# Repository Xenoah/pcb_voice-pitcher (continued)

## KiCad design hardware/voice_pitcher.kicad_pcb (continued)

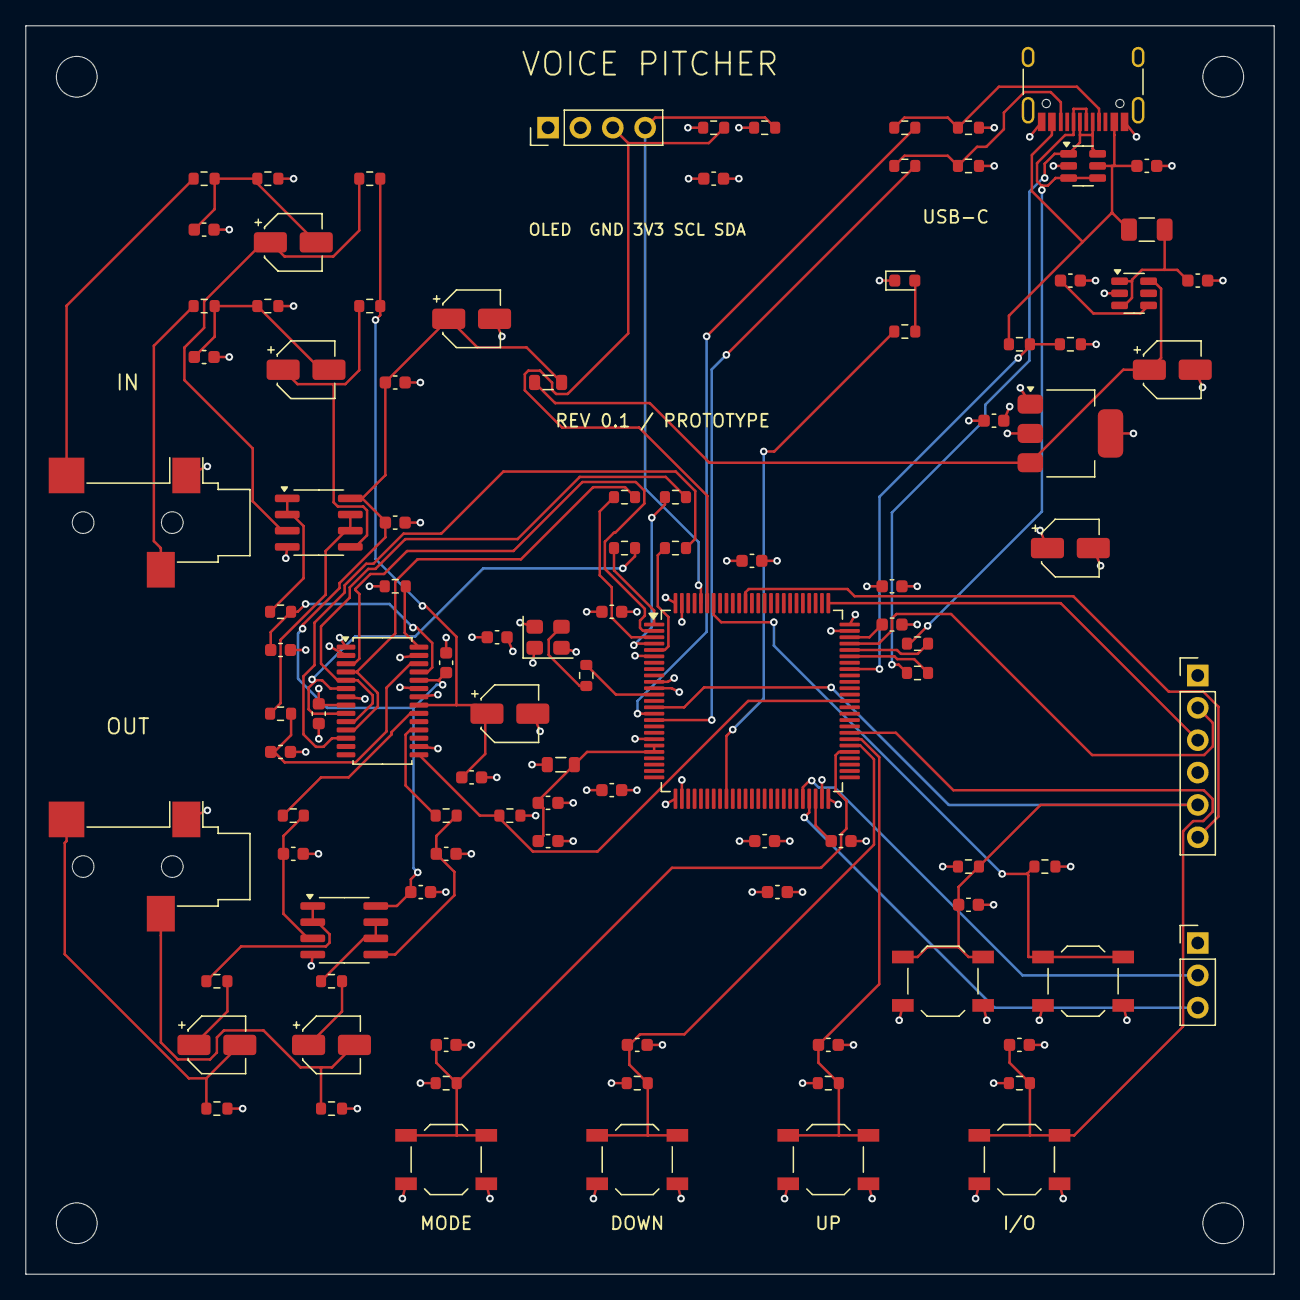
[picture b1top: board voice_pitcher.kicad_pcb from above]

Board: 4 copper layers, 98.0 x 98.0 mm, 107 parts (0 on the bottom side), 68 nets.

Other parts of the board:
H1, H2, H3, H4: M3 NPTH; MountingHole__MountingHole_3.2mm_M3

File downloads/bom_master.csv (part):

ref,value,mpn,lcsc,footprint,assembly,sourcing_status,source_url
C1,100n,CC0603KRX7R9BB104,C14663,Capacitor_SMD:C_0603_1608Metric,SMT,BASIC,https://jlcpcb.com/partdetail/C14663
C2,10u,UWT1C100MCL1GB,,Capacitor_SMD:CP_Elec_4x5.8,SMT,UNVERIFIED,
C3,10u,UWT1C100MCL1GB,,Capacitor_SMD:CP_Elec_4x5.8,SMT,UNVERIFIED,
C4,100n,CC0603KRX7R9BB104,C14663,Capacitor_SMD:C_0603_1608Metric,SMT,BASIC,https://jlcpcb.com/partdetail/C14663
C5,10u,UWT1C100MCL1GB,,Capacitor_SMD:CP_Elec_4x5.8,SMT,UNVERIFIED,
C6,100n,CC0603KRX7R9BB104,C14663,Capacitor_SMD:C_0603_1608Metric,SMT,BASIC,https://jlcpcb.com/partdetail/C14663
C7,100n,CC0603KRX7R9BB104,C14663,Capacitor_SMD:C_0603_1608Metric,SMT,BASIC,https://jlcpcb.com/partdetail/C14663
C8,100n,CC0603KRX7R9BB104,C14663,Capacitor_SMD:C_0603_1608Metric,SMT,BASIC,https://jlcpcb.com/partdetail/C14663
C9,100n,CC0603KRX7R9BB104,C14663,Capacitor_SMD:C_0603_1608Metric,SMT,BASIC,https://jlcpcb.com/partdetail/C14663
C10,100n,CC0603KRX7R9BB104,C14663,Capacitor_SMD:C_0603_1608Metric,SMT,BASIC,https://jlcpcb.com/partdetail/C14663
C11,100n,CC0603KRX7R9BB104,C14663,Capacitor_SMD:C_0603_1608Metric,SMT,BASIC,https://jlcpcb.com/partdetail/C14663
C12,100n,CC0603KRX7R9BB104,C14663,Capacitor_SMD:C_0603_1608Metric,SMT,BASIC,https://jlcpcb.com/partdetail/C14663
C13,1u,GRM188R71C105KA12D,,Capacitor_SMD:C_0603_1608Metric,SMT,UNVERIFIED,
C14,2.2u,GRM188R61C225KE15D,,Capacitor_SMD:C_0603_1608Metric,SMT,UNVERIFIED,
C15,2.2u,GRM188R61C225KE15D,,Capacitor_SMD:C_0603_1608Metric,SMT,UNVERIFIED,
C16,4.7u,GRM188R61C475KE11D,,Capacitor_SMD:C_0603_1608Metric,SMT,UNVERIFIED,
C17,100n,CC0603KRX7R9BB104,C14663,Capacitor_SMD:C_0603_1608Metric,SMT,BASIC,https://jlcpcb.com/partdetail/C14663
C18,100n,CC0603KRX7R9BB104,C14663,Capacitor_SMD:C_0603_1608Metric,SMT,BASIC,https://jlcpcb.com/partdetail/C14663
C19,100n,CC0603KRX7R9BB104,C14663,Capacitor_SMD:C_0603_1608Metric,SMT,BASIC,https://jlcpcb.com/partdetail/C14663
C20,100n,CC0603KRX7R9BB104,C14663,Capacitor_SMD:C_0603_1608Metric,SMT,BASIC,https://jlcpcb.com/partdetail/C14663
C21,10u,UWT1C100MCL1GB,,Capacitor_SMD:CP_Elec_4x5.8,SMT,UNVERIFIED,
C22,100n,CC0603KRX7R9BB104,C14663,Capacitor_SMD:C_0603_1608Metric,SMT,BASIC,https://jlcpcb.com/partdetail/C14663
C23,100n,CC0603KRX7R9BB104,C14663,Capacitor_SMD:C_0603_1608Metric,SMT,BASIC,https://jlcpcb.com/partdetail/C14663
C24,470p,GRM1885C1H471JA01D,,Capacitor_SMD:C_0603_1608Metric,SMT,UNVERIFIED,
C25,4.7u,UWT1C4R7MCL1GB,,Capacitor_SMD:CP_Elec_4x5.8,SMT,UNVERIFIED,
C26,2.2n,GRM1885C1H222JA01D,,Capacitor_SMD:C_0603_1608Metric,SMT,UNVERIFIED,
C29,470p,GRM1885C1H471JA01D,,Capacitor_SMD:C_0603_1608Metric,SMT,UNVERIFIED,
C30,4.7u,UWT1C4R7MCL1GB,,Capacitor_SMD:CP_Elec_4x5.8,SMT,UNVERIFIED,
C31,2.2n,GRM1885C1H222JA01D,,Capacitor_SMD:C_0603_1608Metric,SMT,UNVERIFIED,
C34,100n,CC0603KRX7R9BB104,C14663,Capacitor_SMD:C_0603_1608Metric,SMT,BASIC,https://jlcpcb.com/partdetail/C14663
C35,1n,GRM1885C1H102JA01D,,Capacitor_SMD:C_0603_1608Metric,SMT,UNVERIFIED,
C36,10u,UWT1C100MCL1GB,,Capacitor_SMD:CP_Elec_4x5.8,SMT,UNVERIFIED,
C40,1n,GRM1885C1H102JA01D,,Capacitor_SMD:C_0603_1608Metric,SMT,UNVERIFIED,
C41,10u,UWT1C100MCL1GB,,Capacitor_SMD:CP_Elec_4x5.8,SMT,UNVERIFIED,
C42,100n,CC0603KRX7R9BB104,C14663,Capacitor_SMD:C_0603_1608Metric,SMT,BASIC,https://jlcpcb.com/partdetail/C14663
C43,100n,CC0603KRX7R9BB104,C14663,Capacitor_SMD:C_0603_1608Metric,SMT,BASIC,https://jlcpcb.com/partdetail/C14663
C44,100n,CC0603KRX7R9BB104,C14663,Capacitor_SMD:C_0603_1608Metric,SMT,BASIC,https://jlcpcb.com/partdetail/C14663
C45,100n,CC0603KRX7R9BB104,C14663,Capacitor_SMD:C_0603_1608Metric,SMT,BASIC,https://jlcpcb.com/partdetail/C14663
C46,100n,CC0603KRX7R9BB104,C14663,Capacitor_SMD:C_0603_1608Metric,SMT,BASIC,https://jlcpcb.com/partdetail/C14663
C47,1u,GRM188R71C105KA12D,,Capacitor_SMD:C_0603_1608Metric,SMT,UNVERIFIED,
C48,10n,GRM188R71E103KA01D,,Capacitor_SMD:C_0603_1608Metric,SMT,UNVERIFIED,
D1,GREEN,LTST-C190KGKT,,LED_SMD:LED_0603_1608Metric,SMT,UNVERIFIED,
F1,500mA PTC,1206L050YR,,Fuse:Fuse_1206_3216Metric,SMT,UNVERIFIED,
FB1,120R@100MHz,BLM21PG121SN1D,,Inductor_SMD:L_0805_2012Metric,SMT,UNVERIFIED,
FB2,120R@100MHz,BLM21PG121SN1D,,Inductor_SMD:L_0805_2012Metric,SMT,UNVERIFIED,
H1,M3 NPTH,M3 NPTH,,MountingHole:MountingHole_3.2mm_M3,MECHANICAL,MECHANICAL,
H2,M3 NPTH,M3 NPTH,,MountingHole:MountingHole_3.2mm_M3,MECHANICAL,MECHANICAL,
H3,M3 NPTH,M3 NPTH,,MountingHole:MountingHole_3.2mm_M3,MECHANICAL,MECHANICAL,
H4,M3 NPTH,M3 NPTH,,MountingHole:MountingHole_3.2mm_M3,MECHANICAL,MECHANICAL,
J1,USB-C USB2 DEVICE,TYPE-C-31-M-12,C165948,Connector_USB:USB_C_Receptacle_HRO_TYPE-C-31-M-12,SMT,JLC_LISTED,https://jlcpcb.com/partdetail/C165948
J2,3.5mm STEREO IN,SJ-3523-SMT-TR,,Connector_Audio:Jack_3.5mm_CUI_SJ-3523-SMT_Horizontal,SMT,UNVERIFIED,
J3,3.5mm STEREO OUT,SJ-3523-SMT-TR,,Connector_Audio:Jack_3.5mm_CUI_SJ-3523-SMT_Horizontal,SMT,UNVERIFIED,
J4,OLED GND VCC SCL SDA,1x4 2.54mm OLED socket,,Connector_PinHeader_2.54mm:PinHeader_1x04_P2.54mm_Vertical,HAND,HAND,
J5,SWD,1x6 2.54mm header,,Connector_PinHeader_2.54mm:PinHeader_1x06_P2.54mm_Vertical,HAND,HAND,
J6,UART 3V3,1x3 2.54mm header,,Connector_PinHeader_2.54mm:PinHeader_1x03_P2.54mm_Vertical,HAND,HAND,
R1,5.1k,0603WAF5101T5E,C23186,Resistor_SMD:R_0603_1608Metric,SMT,BASIC,https://jlcpcb.com/partdetail/C23186
R2,5.1k,0603WAF5101T5E,C23186,Resistor_SMD:R_0603_1608Metric,SMT,BASIC,https://jlcpcb.com/partdetail/C23186
R3,1k,0603WAF1001T5E,C21190,Resistor_SMD:R_0603_1608Metric,SMT,BASIC,https://jlcpcb.com/partdetail/C21190
R4,1k,0603WAF1001T5E,C21190,Resistor_SMD:R_0603_1608Metric,SMT,BASIC,https://jlcpcb.com/partdetail/C21190
R5,22,0603WAF220JT5E,C23345,Resistor_SMD:R_0603_1608Metric,SMT,BASIC,https://jlcpcb.com/partdetail/C23345
R6,22,0603WAF220JT5E,C23345,Resistor_SMD:R_0603_1608Metric,SMT,BASIC,https://jlcpcb.com/partdetail/C23345
R7,100k,0603WAF1003T5E,C25803,Resistor_SMD:R_0603_1608Metric,SMT,BASIC,https://jlcpcb.com/partdetail/C25803
R8,100k,0603WAF1003T5E,C25803,Resistor_SMD:R_0603_1608Metric,SMT,BASIC,https://jlcpcb.com/partdetail/C25803
R9,33,0603WAF330JT5E,C23140,Resistor_SMD:R_0603_1608Metric,SMT,JLC_LISTED,https://jlcpcb.com/partdetail/C23140
R10,10k,0603WAF1002T5E,C25804,Resistor_SMD:R_0603_1608Metric,SMT,BASIC,https://jlcpcb.com/partdetail/C25804
R11,10k,0603WAF1002T5E,C25804,Resistor_SMD:R_0603_1608Metric,SMT,BASIC,https://jlcpcb.com/partdetail/C25804
R12,220k,0603WAF2203T5E,C22961,Resistor_SMD:R_0603_1608Metric,SMT,JLC_LISTED,https://jlcpcb.com/partdetail/C22961
R13,10k,0603WAF1002T5E,C25804,Resistor_SMD:R_0603_1608Metric,SMT,BASIC,https://jlcpcb.com/partdetail/C25804
R14,33,0603WAF330JT5E,C23140,Resistor_SMD:R_0603_1608Metric,SMT,JLC_LISTED,https://jlcpcb.com/partdetail/C23140
R15,33,0603WAF330JT5E,C23140,Resistor_SMD:R_0603_1608Metric,SMT,JLC_LISTED,https://jlcpcb.com/partdetail/C23140
R16,33,0603WAF330JT5E,C23140,Resistor_SMD:R_0603_1608Metric,SMT,JLC_LISTED,https://jlcpcb.com/partdetail/C23140
R17,33,0603WAF330JT5E,C23140,Resistor_SMD:R_0603_1608Metric,SMT,JLC_LISTED,https://jlcpcb.com/partdetail/C23140
R20,10k,0603WAF1002T5E,C25804,Resistor_SMD:R_0603_1608Metric,SMT,BASIC,https://jlcpcb.com/partdetail/C25804
R21,10k,0603WAF1002T5E,C25804,Resistor_SMD:R_0603_1608Metric,SMT,BASIC,https://jlcpcb.com/partdetail/C25804
R22,100k,0603WAF1003T5E,C25803,Resistor_SMD:R_0603_1608Metric,SMT,BASIC,https://jlcpcb.com/partdetail/C25803
R23,100,0603WAF1000T5E,C22775,Resistor_SMD:R_0603_1608Metric,SMT,BASIC,https://jlcpcb.com/partdetail/C22775
R25,10k,0603WAF1002T5E,C25804,Resistor_SMD:R_0603_1608Metric,SMT,BASIC,https://jlcpcb.com/partdetail/C25804
R26,10k,0603WAF1002T5E,C25804,Resistor_SMD:R_0603_1608Metric,SMT,BASIC,https://jlcpcb.com/partdetail/C25804
R27,100k,0603WAF1003T5E,C25803,Resistor_SMD:R_0603_1608Metric,SMT,BASIC,https://jlcpcb.com/partdetail/C25803
R28,100,0603WAF1000T5E,C22775,Resistor_SMD:R_0603_1608Metric,SMT,BASIC,https://jlcpcb.com/partdetail/C22775
R30,3.3k,0603WAF3301T5E,C22978,Resistor_SMD:R_0603_1608Metric,SMT,BASIC,https://jlcpcb.com/partdetail/C22978
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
